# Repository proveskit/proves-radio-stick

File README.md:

# proves-radio-stick
New repo for working on a USB stick sized LoRa radio module. 

# Design Purpose
Being able to send and receive data using radios is one of the most fundemental functionalities of the satellite system. Right now, if we want to do anything with the radios we need to take a whole flight controller board out and get it setup to send and receive data. It would be nice to have an [RTL-SDR Style](https://www.rtl-sdr.com/buy-rtl-sdr-dvb-t-dongles/) USB dongle that can be used for testing and ground station purposes! 

# Design Requirements
- Employs an RP2040 Microcontroller (V0); RP2350 from V1 onward
- Onboard 3.3 V regulator for the microcontroller (LDO on V0, TPS62085 buck from V1); V2 radio runs from 5 V VBUS via ferrite
- Radio module: RFM9XW slot (V0), EByte E32-400M20S (V1), EByte E22-400M30S (V2)
- SMA Adaptor for the Antenna
- Is as comapct as possible 

# Versions
| Dir | MCU | Radio | Rail | Antenna | Notes |
|---|---|---|---|---|---|
| `provesradiostick_V0` | RP2040 | RFM9XW slot (SX127x) | 3V3 LDO | SMA | Original concept |
| `proves_radio_stick_V1` | RP2350 | EByte E32-400M20S (SX1278, 20 dBm) | 3V3 buck (TPS62085) | SMA | 4-layer 60 x 32.89 mm |
| `proves_radio_stick_V2` | RP2350 | EByte E22-400M30S (SX1268, 30 dBm) — same module as FC v5e | 3V3 buck + 5 V `RF_VCC` from VBUS via ferrite | SMA | 4-layer 80.5 x 32.89 mm; V1 stretched 20.5 mm to fit the 24 x 38.5 mm module |

## V2 radio pinout (RP2350 GPIO)
| E22 pin | Net | GPIO |
|---|---|---|
| NSS / SCK / MOSI / MISO | SPI1_CS0 / SPI1_SCK / SPI1_MOSI / SPI1_MISO | 9 / 10 / 11 / 8 |
| NRST | RF1_RST | 6 |
| BUSY | RF1_IO0 | 14 |
| DIO1 | RF1_IO1 | 15 |
| DIO2 | RF1_IO2 | 16 |
| RXEN / TXEN | RF1_RX_EN / RF1_TX_EN | 20 / 21 |
| VCC | RF_VCC (5 V, VBUS → FB1 → U19 TPS22918 load switch) | — |
| Radio power enable | RF_PWR_EN → U19 ON (10k pull-up to 3V3, default ON) | 18 |

V2 note: at 30 dBm the E22 draws ~650 mA peak on TX, above the 500 mA USB 2.0 default; use a USB 3 or high-current port for sustained TX. The 110 µF behind U19 soft-starts over ~3 ms (CT 1 nF, ~0.19 A inrush) so the host only sees ~11 µF at plug-in. Drive GPIO18 low then high to power-cycle the radio (hold NRST low and SPI lines low while off). V2 drops the 2.54 mm SWD pin header J1; use the JST-SH SWD connector J22. J3 screw terminal is sourced as Cixi Kefa KF128-2.54-10P (LCSC C474928), a 2.54 mm drop-in for the Phoenix MPT 0,5/10-2,54 footprint. J4 header and TP1–TP7 are not populated by JLC. Firmware differs from V1: SX1268 driver with BUSY handshake, not SX1278. Pin numbering differs from FC v5e (v5e uses SPI0 GPIO9-12, BUSY 13, DIO1 14, RXEN 22).

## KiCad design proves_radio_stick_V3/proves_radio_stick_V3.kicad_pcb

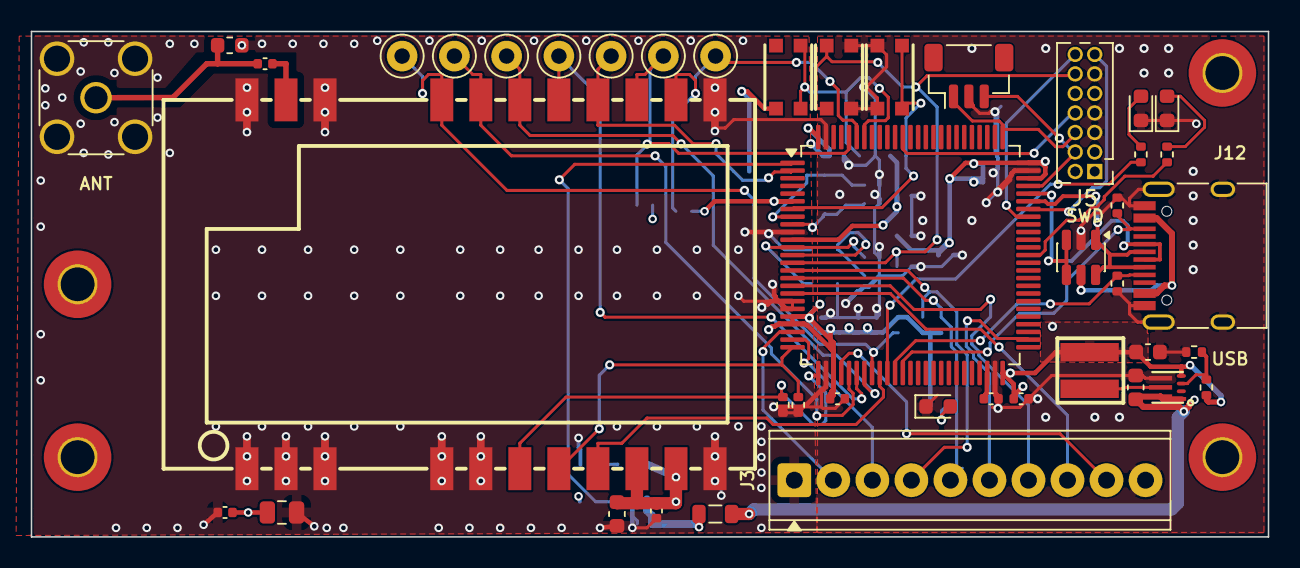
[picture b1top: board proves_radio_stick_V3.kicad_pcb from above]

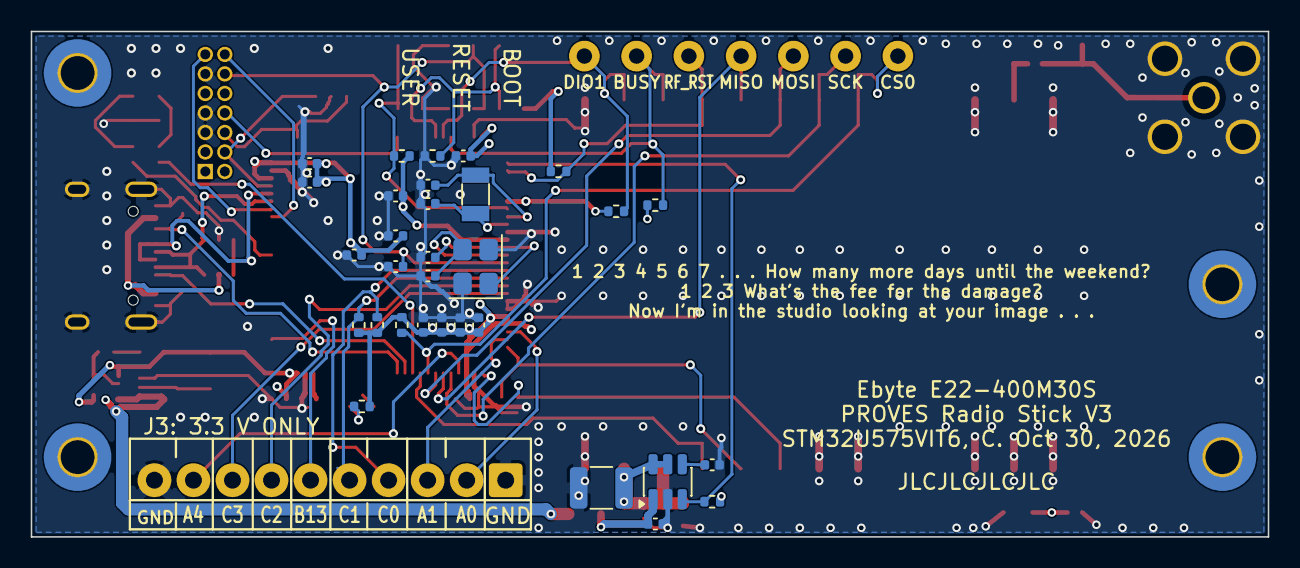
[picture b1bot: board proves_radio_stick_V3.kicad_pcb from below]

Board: 4 copper layers, 80.5 x 32.9 mm, 78 parts (31 on the bottom side), 51 nets.

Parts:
C1, C6, C101, C102, C103, C104, C105, C106, C108, C110, C112, C114: 100nF; C_0402_1005Metric
C3: 47uF; C_0805_2012Metric
C4: 100uF 10V; C_1210_3225Metric
C5, C15: 10uF; C_0603_1608Metric
C7: 100pF; C_0402_1005Metric
C14: 22uF; C_0603_1608Metric
C79: 1nF; C_0402_1005Metric
C80, C109, C111: 1uF; C_0402_1005Metric
C107, C113: 4.7uF; C_0402_1005Metric
C115, C116: 12pF; C_0402_1005Metric
C117, C118: 10pF; C_0402_1005Metric
D1, D2, D3: LED; LED_0603_1608Metric
FB1: BLM21PG600SN1D; L_0805_2012Metric
H1, H2, H3, H4: MountingHole; MountingHole_2.2mm_M2_Pad_TopBottom
J2: SMA antenna; SMA_Amphenol_132134_Vertical
J3: J3 breakout; TerminalBlock_Phoenix_MPT-0,5-10-2.54_1x10_P2.54mm_Horizont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
J5: STDC14; PinHeader_2x07_P1.27mm_Vertical
J12: USB-C (USB 2.0); USB_C_Receptacle_HRO_TYPE-C-31-M-12
J22: SWD (JST-SH); JST_SH_BM03B-SRSS-TB_1x03-1MP_P1.00mm_Vertical
L1: XFL4015-471MEC; IND-SMD_L4.0-W4.0_XFL4020-102MEB
L2: 120nH; L_0603_1608Metric
R3: 162k; R_0402_1005Metric
R4: 510k; R_0402_1005Metric
R5, R9, R11, R12, R95, R101, R102: 10k; R_0402_1005Metric
R13, R80, R103: 1k; R_0402_1005Metric
R14, R15, R104, R105: 4.7k; R_0402_1005Metric
R26, R27: 5.1k; R_0402_1005Metric
SW1, SW2, SW3: KMR2; BTN_KMR2_4.6X2.8
TP1, TP2, TP3, TP4, TP5, TP6, TP7: TestPoint; TestPoint_Keystone_5000-5004_Miniature
U1: STM32U575VIT6; LQFP-100_14x14mm_P0.5mm
U2: TPS62085RLTR; VSON-7_L2.0-W2.0-P0.5-TL
U3: E22-400M30S; WIRELM-SMD_E22-400M30S
U4: USBLC6-2SC6; SOT-23-6
U19: TPS22918DBVR; SOT-23-6
Y101: 16MHz; Crystal_SMD_3225-4Pin_3.2x2.5mm
Y102: 32.768kHz; Crystal_SMD_3215-2Pin_3.2x1.5mm

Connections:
+3V3: C1.1, C3.1, C14.1, C101.1, C102.1, C103.1, C104.1, C105.1, C106.1, C107.1, C108.1, C109.1, C110.1, C111.1, C112.1, J5.3, L1.2, R4.1, R5.2, R9.2, R14.1, R15.1, R80.1, R95.2, R102.1, R104.1, R105.1, SW1.A, SW1.A', U1.6, U1.11, U1.21, U1.22, U1.28, U1.50, U1.73, U1.75, U1.100, U2.4 (VOS)
/BOOT0: R101.1, SW1.B, SW1.B', U1.94
/LED2_A: D2.2, R103.2
/OSC32_IN: C117.1, U1.8, Y102.1
/OSC32_OUT: C118.1, U1.9, Y102.2
/OSC_IN: C115.1, U1.12, Y101.1
/OSC_OUT: C116.1, U1.13, Y101.3
/RF_ANT: C7.2, J2.1 (In), L2.1
/USER_BTN: R102.2, SW3.B, SW3.B', U1.7
/VCAP: C113.1, U1.48
Firmware_Active: R13.1, U1.35
GND: C1.2, C3.2, C4.2, C5.2, C6.2, C14.2, C15.2, C79.2, C80.2, C101.2, C102.2, C103.2, C104.2, C105.2, C106.2, C107.2, C108.2, C109.2, C110.2, C111.2, C112.2, C113.2, C114.2, C115.2, C116.2, C117.2, C118.2, D1.1 (K), D2.1, D3.1 (K), J2.2 (Ext), J3.1, J3.10, J5.5, J5.7, J5.11, J12.A1 (GND), J12.A12 (GND), J12.B1 (GND), J12.B12 (GND), J12.S1 (SHIELD), J22.2, L2.2, R3.2, R11.1, R12.1, R26.1, R27.1, R101.2, SW2.B, SW2.B', SW3.A, SW3.A', U1.10, U1.19, U1.20, U1.27, U1.49, U1.74, U1.99, U2.5 (GND), U3.1, U3.2, U3.3, U3.4, U3.5, U3.11, U3.12, U3.20, U3.22, U4.2, U19.2, Y101.2, Y101.4
J3_IO1: J3.2, U1.23
J3_IO2: J3.3, U1.24
J3_IO3: J3.4, R104.2, U1.15
J3_IO4: J3.5, R105.2, U1.16
J3_IO5: J3.6, U1.52
J3_IO6: J3.7, U1.17
J3_IO7: J3.8, U1.18
J3_IO8: J3.9, U1.29
unnamed: D1.2 (A), R13.2
unnamed: D3.2 (A), R80.2
unnamed: R3.1, R4.2, U2.3 (FB)
unnamed: L1.1, U2.6 (SW)
unnamed: C7.1, U3.21
unnamed: C79.1, U19.4
RF1_IO0: R14.2, TP5.1, U1.96, U3.14
RF1_IO1: R15.2, TP6.1, U1.95, U3.13
RF1_IO2: U1.34, U3.8
RF1_RST: R5.1, TP7.1, U1.2, U3.15
RF1_RX_EN: R11.2, U1.26, U3.6
RF1_TX_EN: R12.2, U1.25, U3.7
RF_5V_IN: C80.1, FB1.2, U19.1
RF_PWR_EN: R95.1, U1.1, U19.3
RF_VCC: C4.1, C5.1, C6.1, U3.9, U3.10, U19.5, U19.6
RX: J5.13, U1.69
SPI1_CS0: R9.1, TP2.1, U1.33, U3.19
SPI1_MISO: TP1.1, U1.31, U3.16
SPI1_MOSI: TP4.1, U1.32, U3.17
SPI1_SCK: TP3.1, U1.30, U3.18
SWCLK: J5.6, J22.1, U1.76
SWDIO: J5.4, J22.3, U1.72
SWO: J5.8, U1.89
TX: J5.14, U1.68
USB_CC1_SENSE: J12.A5 (CC1), R26.2, U1.36
USB_CC2_SENSE: J12.B5 (CC2), R27.2, U1.37
USB_D+: J12.A6 (D+), J12.B6 (D+), U1.71, U4.3, U4.4
USB_D-: J12.A7 (D-), J12.B7 (D-), U1.70, U4.1, U4.6
USER_LED: R103.1, U1.63
VBUS: C15.1, FB1.1, J12.A4 (VBUS), J12.A9 (VBUS), J12.B4 (VBUS), J12.B9 (VBUS), U2.1 (EN), U2.7 (VIN), U4.5
~RESET: C114.1, J5.12, SW2.A, SW2.A', U1.14

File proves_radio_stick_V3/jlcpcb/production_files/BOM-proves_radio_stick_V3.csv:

Comment,Designator,Footprint,LCSC,Quantity
100n,"C1,C101,C102,C103,C104,C105,C106,C108,C110,C112,C114",C_0402_1005Metric,C1525,11
47uF,C3,C_0805_2012Metric,C16780,1
100uF 10V,C4,C_1210_3225Metric,C84455,1
10uF,"C5,C15",C_0603_1608Metric,C19702,2
100nF,C6,C_0402_1005Metric,C1525,1
100pF,C7,C_0402_1005Metric,C1546,1
22uF,C14,C_0603_1608Metric,C59461,1
1nF,C79,C_0402_1005Metric,C1523,1
1uF,C80,C_0402_1005Metric,C52923,1
4.7u,"C107,C113",C_0402_1005Metric,C23733,2
1u,"C109,C111",C_0402_1005Metric,C52923,2
12p,"C115,C116",C_0402_1005Metric,C1547,2
10p,"C117,C118",C_0402_1005Metric,C32949,2
LED,"D1,D2,D3",LED_0603_1608Metric,C2290,3
BLM21PG600SN1D,FB1,L_0805_2012Metric,C18305,1
Conn_Coaxial,J2,SMA_Amphenol_132134_Vertical,C3174425,1
Screw_Terminal_01x10,J3,"TerminalBlock_Phoenix_MPT-0,5-10-2.54_1x10_P2.54mm_Horizontal",C474928,1
STDC14,J5,PinHeader_2x07_P1.27mm_Vertical,C22438122,1
USB_C_Receptacle_USB2.0_16P,J12,USB_C_Receptacle_HRO_TYPE-C-31-M-12,C165948,1
SWD Port,J22,JST_SH_BM03B-SRSS-TB_1x03-1MP_P1.00mm_Vertical,C160389,1
XFL4015-471MEC,L1,IND-SMD_L4.0-W4.0_XFL4020-102MEB,C18221164,1
120nH,L2,L_0603_1608Metric,C86138,1
162k,R3,R_0402_1005Metric,C54068,1
510k,R4,R_0402_1005Metric,C11616,1
10k,"R5,R9,R11,R12,R95,R101,R102",R_0402_1005Metric,C25744,7
1k,"R13,R80,R103",R_0402_1005Metric,C11702,3
5.1k,"R26,R27",R_0402_1005Metric,C25905,2
4.7k,"R104,R105",R_0402_1005Metric,C25900,2
KMR2,"SW1,SW2,SW3",BTN_KMR2_4.6X2.8,C72443,3
STM32U575VIT6,U1,LQFP-100_14x14mm_P0.5mm,C5270999,1
TPS62085RLTR,U2,VSON-7_L2.0-W2.0-P0.5-TL,C130072,1
E22-400M30S,U3,WIRELM-SMD_E22-400M30S,C411292,1
USBLC6-2SC6,U4,SOT-23-6,C7519,1
TPS22918DBVR,U19,SOT-23-6,C131941,1
16MHz,Y101,Crystal_SMD_3225-4Pin_3.2x2.5mm,C13738,1
32.768kHz,Y102,Crystal_SMD_3215-2Pin_3.2x1.5mm,C97604,1

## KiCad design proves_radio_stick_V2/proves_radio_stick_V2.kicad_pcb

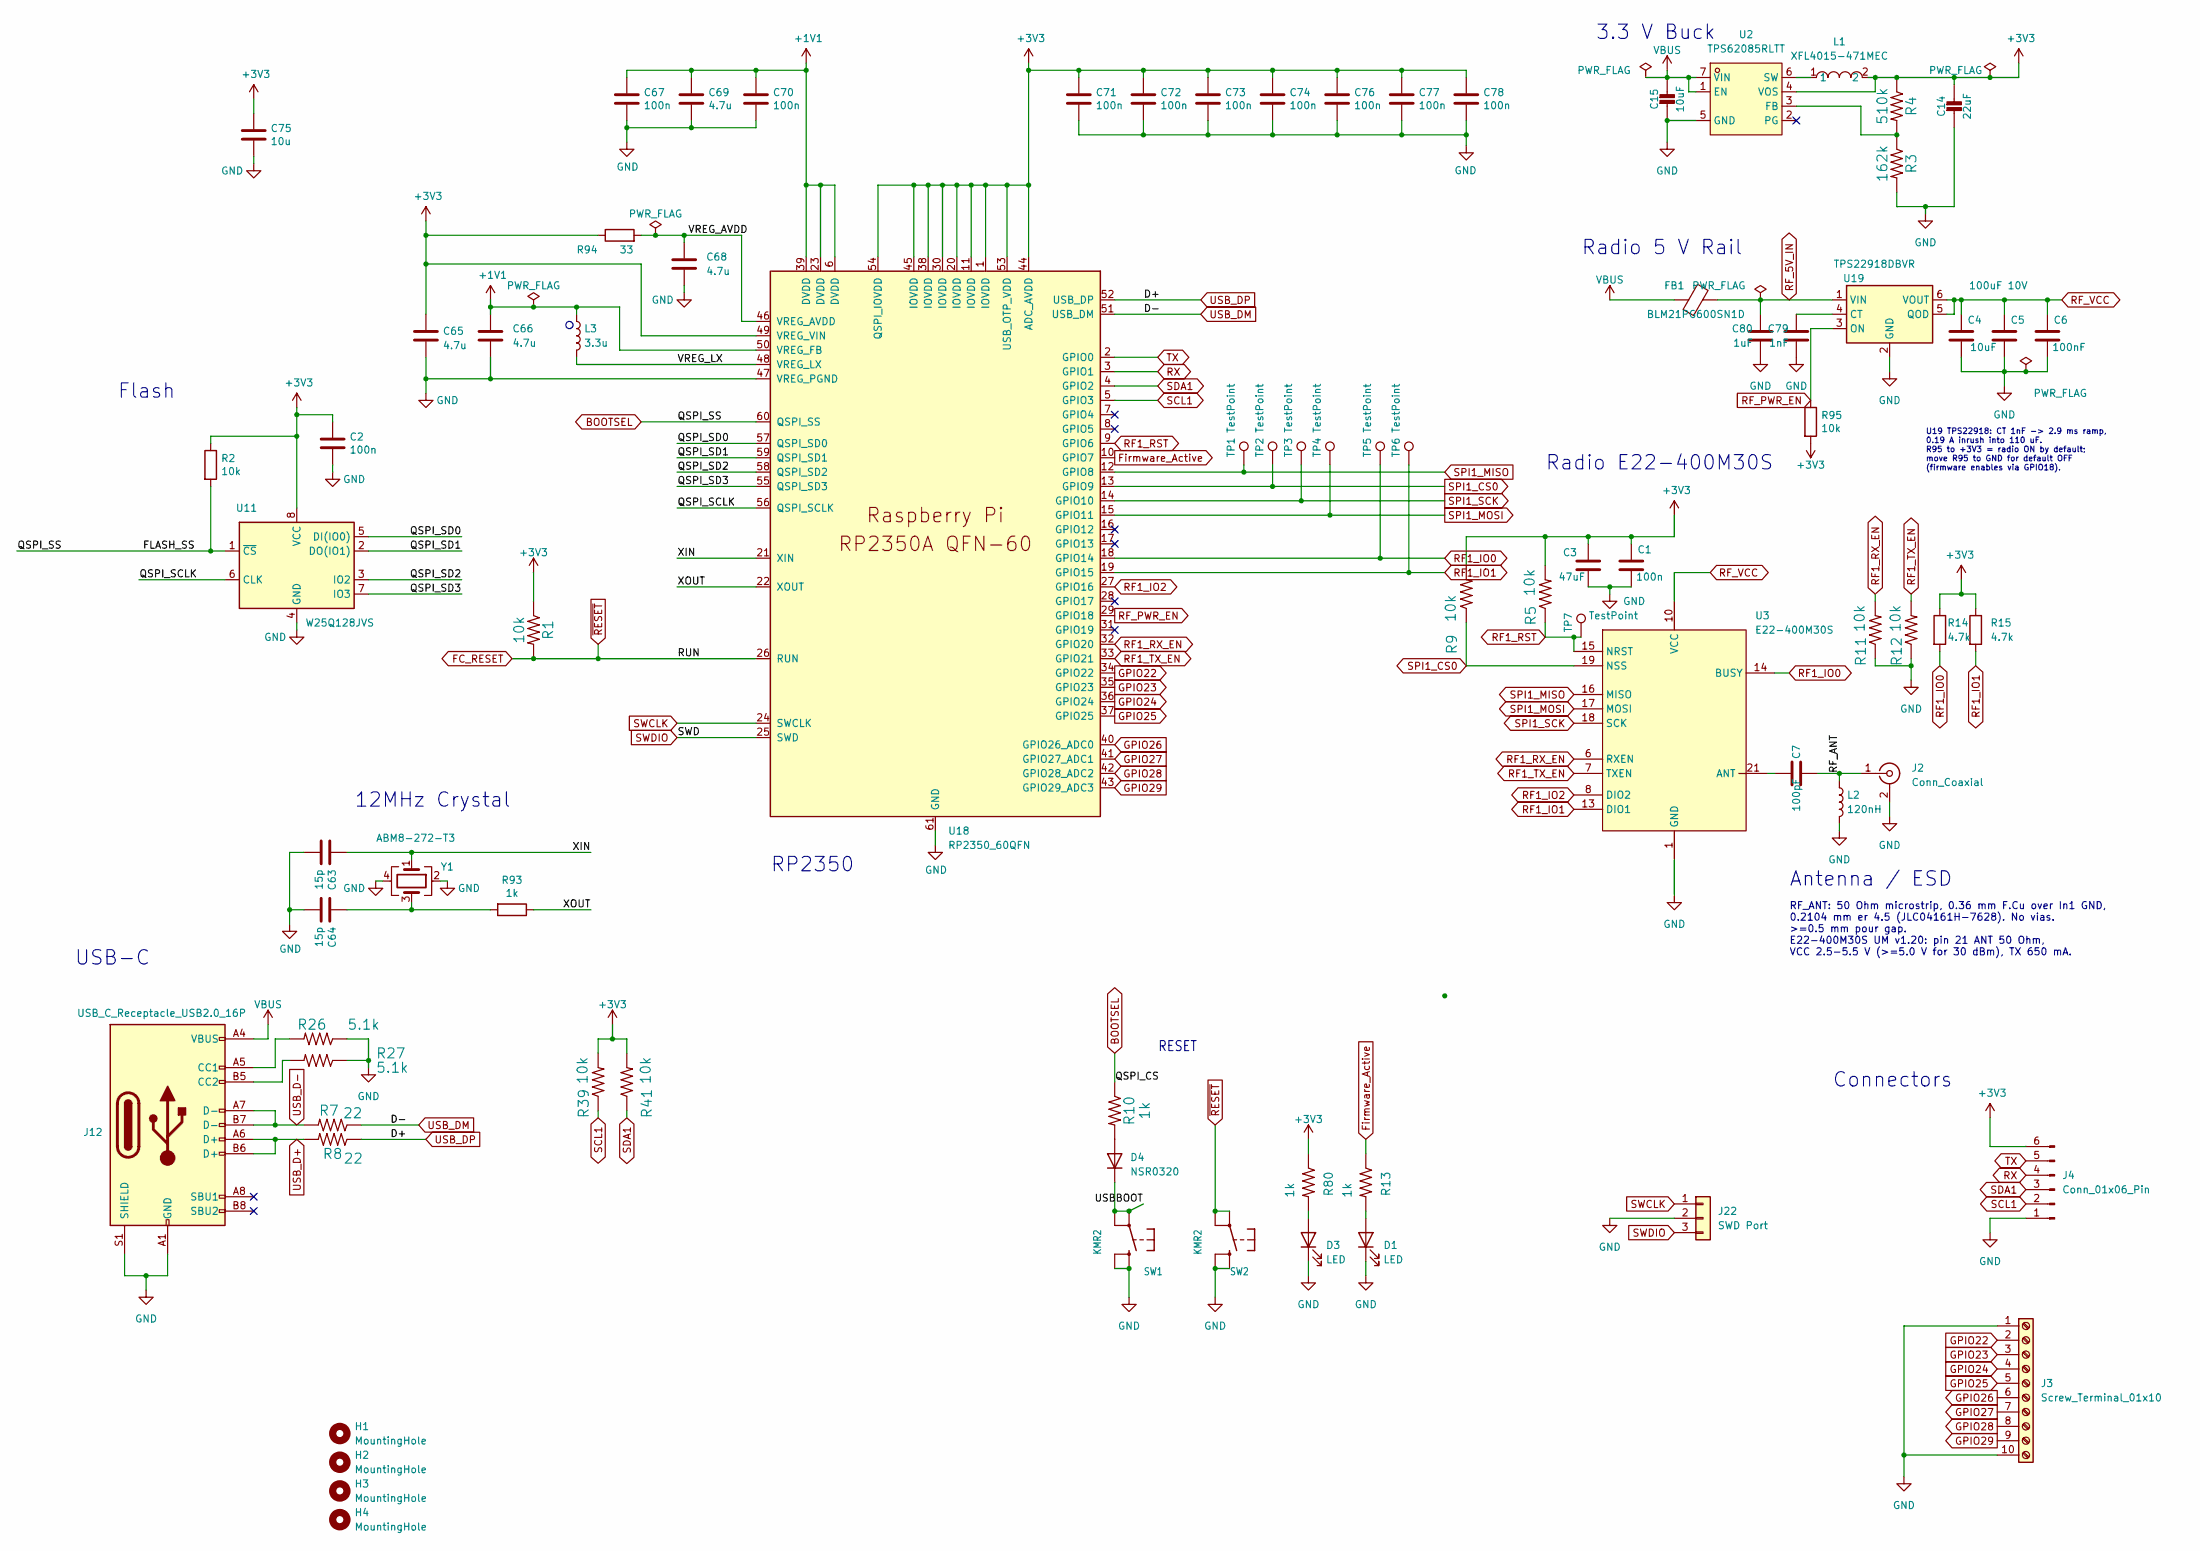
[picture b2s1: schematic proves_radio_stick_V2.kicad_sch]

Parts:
C1, C2, C67, C70, C71, C72, C73, C74, C76, C77, C78: 100n; C_0402_1005Metric; LCSC Part C1525
C3: 47uF; C_0805_2012Metric; LCSC Part C16780
C4: 100uF 10V; C_1210_3225Metric; LCSC Part C84455
C5, C15: 10uF; C_0603_1608Metric; LCSC Part C19702
C6: 100nF; C_0402_1005Metric; LCSC Part C1525
C7: 100pF; C_0402_1005Metric; LCSC Part C1546
C14: 22uF; C_0603_1608Metric; LCSC Part C59461
C63, C64: 15p; C_0402_1005Metric; LCSC Part C1548
C65, C66: 4.7u; C_0402_1005Metric_small_pads; LCSC Part C23733
C68, C69: 4.7u; C_0402_1005Metric; LCSC Part C23733
C75: 10u; C_0603_1608Metric; LCSC Part C19702
C79: 1nF; C_0402_1005Metric; LCSC Part C1523
C80: 1uF; C_0402_1005Metric; LCSC Part C52923
D1, D3: LED; LED_0603_1608Metric; LCSC Part C2290
D4: NSR0320; D_SOD-323F; LCSC Part C48192
FB1: BLM21PG600SN1D; L_0805_2012Metric; LCSC Part C18305
H1, H2, H3, H4: MountingHole; MountingHole_2.2mm_M2_Pad_TopBottom
J2: Conn_Coaxial; SMA_Amphenol_132134_Vertical; LCSC Part C3174425
J3: Screw_Terminal_01x10; TerminalBlock_Phoenix_MPT-0,5-10-2.54_1x10_P2.54mm_Horizont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; MPN KF128-2.54-10P; LCSC Part C474928
J4: Conn_01x06_Pin; PinHeader_1x06_P2.54mm_Vertical
J12: USB_C_Receptacle_USB2.0_16P; USB_C_Receptacle_HRO_TYPE-C-31-M-12; LCSC Part C165948
J22: SWD Port; JST_SH_BM03B-SRSS-TB_1x03-1MP_P1.00mm_Vertical; LCSC Part C160389
L1: XFL4015-471MEC; IND-SMD_L4.0-W4.0_XFL4020-102MEB; LCSC Part C18221164
L2: 120nH; L_0603_1608Metric; MPN LQW18ANR12G00D; LCSC Part C86138
L3: 3.3u; L_pol_2016; LCSC Part C42411119
R1, R2, R5, R9, R11, R12, R39, R41, R95: 10k; R_0402_1005Metric; LCSC Part C25744
R3: 162k; R_0402_1005Metric; LCSC Part C54068
R4: 510k; R_0402_1005Metric; LCSC Part C11616
R7, R8: 22; R_0402_1005Metric; LCSC Part C25092
R10, R13, R80, R93: 1k; R_0402_1005Metric; LCSC Part C11702
R14, R15: 4.7k; R_0402_1005Metric; LCSC Part C25900
R26, R27: 5.1k; R_0402_1005Metric; LCSC Part C25905
R94: 33; R_0402_1005Metric; LCSC Part C25105
SW1, SW2: KMR2; BTN_KMR2_4.6X2.8; LCSC Part C72443
TP1, TP2, TP3, TP4, TP5, TP6, TP7: TestPoint; TestPoint_Keystone_5000-5004_Miniature
U2: TPS62085RLTT; VSON-7_L2.0-W2.0-P0.5-TL; LCSC Part C2070694
U3: E22-400M30S; WIRELM-SMD_E22-400M30S; MPN E22-400M30S; LCSC Part C411292
U11: W25Q128JVS; SOIC-8_5.3x5.3mm_P1.27mm; LCSC Part C97521
U18: RP2350_60QFN; RP2350-QFN-60-1EP_7x7_P0.4mm_EP3.4x3.4mm_ThermalVias; LCSC Part C42411118
U19: TPS22918DBVR; SOT-23-6; LCSC Part C131941
Y1: ABM8-272-T3; Crystal_SMD_3225-4Pin_3.2x2.5mm; LCSC Part C20625731

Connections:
+1V1: C66.1, C67.1, C69.1, C70.1, L3.1, U18.6 (DVDD), U18.23 (DVDD), U18.39 (DVDD), U18.50 (VREG_FB)
+3V3: C1.1, C2.1, C3.1, C14.1, C65.1, C71.1, C72.1, C73.1, C74.1, C75.1, C76.1, C77.1, C78.1, J4.6, L1.2, R1.1, R2.1, R4.1, R5.2, R9.2, R14.1, R15.1, R39.2, R41.2, R80.1, R94.1, R95.2, U2.4 (VOS), U11.8 (VCC), U18.1 (IOVDD), U18.11 (IOVDD), U18.20 (IOVDD), U18.30 (IOVDD), U18.38 (IOVDD), U18.44 (ADC_AVDD), U18.45 (IOVDD), U18.49 (VREG_VIN), U18.53 (USB_OTP_VDD), U18.54 (QSPI_IOVDD)
/QSPI_SCLK: U11.6 (CLK), U18.56 (QSPI_SCLK)
/QSPI_SD0: U11.5 (DI(IO0)), U18.57 (QSPI_SD0)
/QSPI_SD1: U11.2 (DO(IO1)), U18.59 (QSPI_SD1)
/QSPI_SD2: U11.3 (IO2), U18.58 (QSPI_SD2)
/QSPI_SD3: U11.7 (IO3), U18.55 (QSPI_SD3)
/RF_ANT: C7.2, J2.1 (In), L2.1
/USBBOOT: D4.1 (K), SW1.A, SW1.A' (P1)
/VREG_AVDD: C68.1, R94.2, U18.46 (VREG_AVDD)
/VREG_LX: L3.2, U18.48 (VREG_LX)
/XIN: C63.1, U18.21 (XIN), Y1.1
/XOUT: R93.1, U18.22 (XOUT)
BOOTSEL: R2.2, R10.1, U11.1 (~CS), U18.60 (QSPI_SS)
FC_RESET: R1.2, SW2.A, SW2.A' (P1), U18.26 (RUN)
Firmware_Active: R13.1, U18.10 (GPIO7)
GND: C1.2, C2.2, C3.2, C4.2, C5.2, C6.2, C14.2, C15.2, C63.2, C64.2, C65.2, C66.2, C67.2, C68.2, C69.2, C70.2, C71.2, C72.2, C73.2, C74.2, C75.2, C76.2, C77.2, C78.2, C79.2, C80.2, D1.1 (K), D3.1 (K), J2.2 (Ext), J3.1, J3.10, J4.1, J12.A1 (GND), J12.A12 (GND), J12.B1 (GND), J12.B12 (GND), J12.S1 (SHIELD), J22.2, L2.2, R3.2, R11.1, R12.1, R26.1, R27.1, SW1.B (S), SW1.B' (S1), SW2.B (S), SW2.B' (S1), U2.5 (GND), U3.1 (GND), U3.2 (GND), U3.3 (GND), U3.4 (GND), U3.5 (GND), U3.11 (GND), U3.12 (GND), U3.20 (GND), U3.22 (GND), U11.4 (GND), U18.47 (VREG_PGND), U18.61 (GND), U19.2 (GND), Y1.2, Y1.4
GPIO22: J3.2, U18.34 (GPIO22)
GPIO23: J3.3, U18.35 (GPIO23)
GPIO24: J3.4, U18.36 (GPIO24)
GPIO25: J3.5, U18.37 (GPIO25)
GPIO26: J3.6, U18.40 (GPIO26_ADC0)
GPIO27: J3.7, U18.41 (GPIO27_ADC1)
GPIO28: J3.8, U18.42 (GPIO28_ADC2)
GPIO29: J3.9, U18.43 (GPIO29_ADC3)
unnamed: C64.1, R93.2, Y1.3
unnamed: D1.2 (A), R13.2
unnamed: D3.2 (A), R80.2
unnamed: D4.2 (A), R10.2
unnamed: J12.A5 (CC1), R26.2
unnamed: J12.B5 (CC2), R27.2
unnamed: R3.1, R4.2, U2.3 (FB)
unnamed: L1.1, U2.6 (SW)
unnamed: C7.1, U3.21 (ANT)
unnamed: C79.1, U19.4 (CT)
RF1_IO0: R14.2, TP5.1, U3.14 (BUSY), U18.18 (GPIO14)
RF1_IO1: R15.2, TP6.1, U3.13 (DIO1), U18.19 (GPIO15)
RF1_IO2: U3.8 (DIO2), U18.27 (GPIO16)
RF1_RST: R5.1, TP7.1, U3.15 (NRST), U18.9 (GPIO6)
RF1_RX_EN: R11.2, U3.6 (RXEN), U18.32 (GPIO20)
RF1_TX_EN: R12.2, U3.7 (TXEN), U18.33 (GPIO21)
RF_5V_IN: C80.1, FB1.2, U19.1 (VIN)
RF_PWR_EN: R95.1, U18.29 (GPIO18), U19.3 (ON)
RF_VCC: C4.1, C5.1, C6.1, U3.9 (VCC), U3.10 (VCC), U19.5 (QOD), U19.6 (VOUT)
RX: J4.4, U18.3 (GPIO1)
SCL1: J4.2, R39.1, U18.5 (GPIO3)
SDA1: J4.3, R41.1, U18.4 (GPIO2)
SPI1_CS0: R9.1, TP2.1, U3.19 (NSS), U18.13 (GPIO9)
SPI1_MISO: TP1.1, U3.16 (MISO), U18.12 (GPIO8)
SPI1_MOSI: TP4.1, U3.17 (MOSI), U18.15 (GPIO11)
SPI1_SCK: TP3.1, U3.18 (SCK), U18.14 (GPIO10)
SWCLK: J22.1, U18.24 (SWCLK)
SWDIO: J22.3, U18.25 (SWD)
TX: J4.5, U18.2 (GPIO0)
USB_D+: J12.A6 (D+), J12.B6 (D+), R8.2
USB_D-: J12.A7 (D-), J12.B7 (D-), R7.2
USB_DM: R7.1, U18.51 (USB_DM)
USB_DP: R8.1, U18.52 (USB_DP)
VBUS: C15.1, FB1.1, J12.A4 (VBUS), J12.A9 (VBUS), J12.B4 (VBUS), J12.B9 (VBUS), U2.1 (EN), U2.7 (VIN)

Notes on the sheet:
RESET
Flash
12MHz Crystal
RF_ANT: 50 Ohm microstrip, 0.36 mm F.Cu over In1 GND, 0.2104 mm er 4.5 (JLC04161H-7628). No vias. >=0.5 mm pour gap. E22-400M30S UM v1.20: pin 21 ANT 50 Ohm, VCC 2.5-5.5 V (>=5.0 V for 30 dBm), TX 650 mA.
U19 TPS22918: CT 1nF -> 2.9 ms ramp, 0.19 A inrush into 110 uF. R95 to +3V3 = radio ON by default; move R95 to GND for default OFF (firmware enables via GPIO18).
3.3 V Buck
Radio 5 V Rail
Radio E22-400M30S
Antenna / ESD
Connectors
USB-C
RP2350

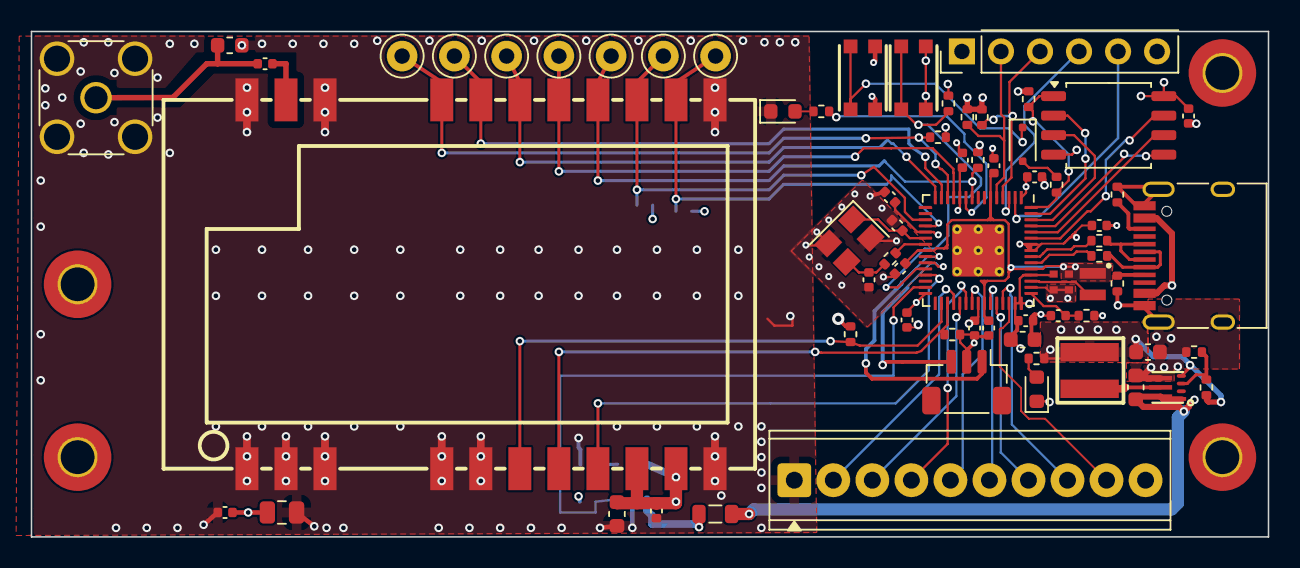
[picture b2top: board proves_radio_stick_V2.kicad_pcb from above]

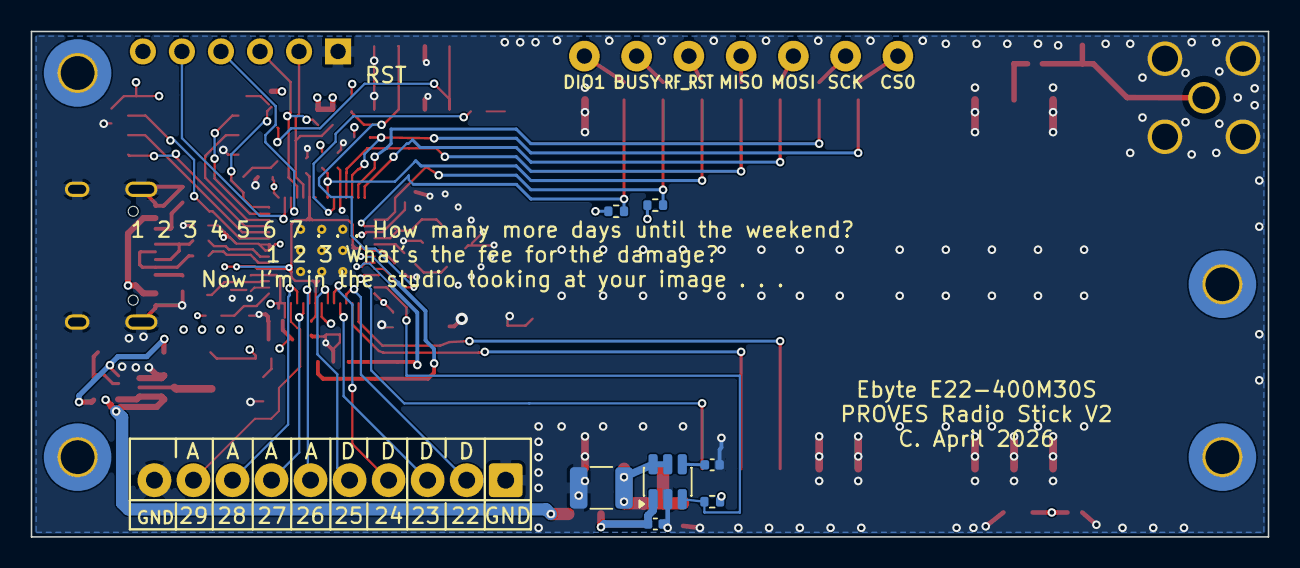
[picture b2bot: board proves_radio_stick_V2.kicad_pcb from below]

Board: 4 copper layers, 80.5 x 32.9 mm, 80 parts (7 on the bottom side), 59 nets.

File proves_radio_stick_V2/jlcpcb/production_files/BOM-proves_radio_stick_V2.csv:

Comment,Designator,Footprint,LCSC,Quantity
100uF 10V,C4,C_1210_3225Metric,C84455,1
1nF,C79,C_0402_1005Metric,C1523,1
1uF,C80,C_0402_1005Metric,C52923,1
4.7k,"R14,R15",R_0402_1005Metric,C25900,2
10k,"R95,R1,R2,R5,R9,R11,R12,R39,R41",R_0402_1005Metric,C25744,9
TPS22918DBVR,U19,SOT-23-6,C131941,1
100n,"C1,C2,C67,C70,C71,C72,C73,C74,C76,C77,C78",C_0402_1005Metric,C1525,11
47uF,C3,C_0805_2012Metric,C16780,1
10uF,"C5,C15",C_0603_1608Metric,C19702,2
100nF,C6,C_0402_1005Metric,C1525,1
100pF,C7,C_0402_1005Metric,C1546,1
22uF,C14,C_0603_1608Metric,C59461,1
15p,"C63,C64",C_0402_1005Metric,C1548,2
4.7u,"C65,C66",C_0402_1005Metric_small_pads,C23733,2
4.7u,"C68,C69",C_0402_1005Metric,C23733,2
10u,C75,C_0603_1608Metric,C19702,1
LED,"D1,D3",LED_0603_1608Metric,C2290,2
NSR0320,D4,D_SOD-323F,C48192,1
BLM21PG600SN1D,FB1,L_0805_2012Metric,C18305,1
Conn_Coaxial,J2,SMA_Amphenol_132134_Vertical,C3174425,1
Screw_Terminal_01x10,J3,"TerminalBlock_Phoenix_MPT-0,5-10-2.54_1x10_P2.54mm_Horizontal",C474928,1
USB_C_Receptacle_USB2.0_16P,J12,USB_C_Receptacle_HRO_TYPE-C-31-M-12,C165948,1
SWD Port,J22,JST_SH_BM03B-SRSS-TB_1x03-1MP_P1.00mm_Vertical,C160389,1
XFL4015-471MEC,L1,IND-SMD_L4.0-W4.0_XFL4020-102MEB,C18221164,1
120nH,L2,L_0603_1608Metric,C86138,1
3.3u,L3,L_pol_2016,C42411119,1
162k,R3,R_0402_1005Metric,C54068,1
510k,R4,R_0402_1005Metric,C11616,1
22,"R7,R8",R_0402_1005Metric,C25092,2
1k,"R10,R13,R80,R93",R_0402_1005Metric,C11702,4
5.1k,"R26,R27",R_0402_1005Metric,C25905,2
33,R94,R_0402_1005Metric,C25105,1
KMR2,"SW1,SW2",BTN_KMR2_4.6X2.8,C72443,2
TPS62085RLTT,U2,VSON-7_L2.0-W2.0-P0.5-TL,C2070694,1
E22-400M30S,U3,WIRELM-SMD_E22-400M30S,C411292,1
W25Q128JVS,U11,SOIC-8_5.3x5.3mm_P1.27mm,C97521,1
RP2350_60QFN,U18,RP2350-QFN-60-1EP_7x7_P0.4mm_EP3.4x3.4mm_ThermalVias,C42411118,1
ABM8-272-T3,Y1,Crystal_SMD_3225-4Pin_3.2x2.5mm,C20625731,1

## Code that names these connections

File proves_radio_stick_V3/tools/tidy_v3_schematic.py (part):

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    ('3  RADIO 5 V SWITCH (U19)', [('rail', 237, 22)], [
        ('RF_VCC = VBUS via FB1 and load switch U19 (>= 5 V for 30 dBm).\n'
         'CT 1 nF -> 2.9 ms ramp, 0.19 A inrush into 110 uF.\n'
         'ON = RF_PWR_EN (PE2). R95 to +3V3 = radio ON by default;\n'
         'move R95 to GND for default OFF.', 'rail^', 0, 3.81, 1.27)]),
    ('4  MCU SUPPORT', [('decoup', 17, 112), ('hse', 17, 168), ('lse', 53, 168),
                        ('boot0', 17, 214), ('button', 53, 214)], [
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         '(>= 5.0 V for 30 dBm), TX 650 mA.', 'tps', 58, -2.54, 1.27)]),
    ('7  DEBUG (J5, J22)', [('stdc14', 346, 22), ('swd', 346, 52)], [
        ('J5 STDC14 fits STLINK-V3MINIE.\nPins 13/14 = T_VCP_RX/T_VCP_TX:\n'
         'USART1 PA9 TX / PA10 RX.\nJ22 JST-SH: SWD only (no SWO).', 'swd^', 0, 3.81, 1.27)]),
    ('8  J3 BREAKOUT (screw terminal)', [('j3', 320, 112), ('i2c', 375, 112)], [
        ('I2C3 pull-ups', 'i2c', 0, -3.81, H),
        ('3.3 V logic only: J3_IO1-8 go straight to MCU pins\n'
         '(no buffer or protection). IO3/IO4 = I2C3 SCL/SDA,\n'
         'IO5-IO8 = SPI2. Full map: pinmap/README.md.', 'j3^', 0, 3.81, 1.27)]),
    ('9  RESET AND LEDS', [('reset', 320, 178), ('leds', 340, 178), ('uled', 370, 178)], [
        ('SW2 pulls ~{RESET} (NRST) low. D3 = +3V3 power,\nD1 = Firmware_Active (PB0), D2 = USER_LED (PC6).',
         'leds^', -20, 3.81, 1.27)]),
    ('10  MOUNTING', [('holes', 198, 243)], []),
]
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
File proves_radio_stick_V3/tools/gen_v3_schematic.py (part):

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SUPPLY = [n for n, v in PIN_NAME.items() if v in ('VDD', 'VDDA', 'VDDUSB', 'VBAT')]
GROUND = [n for n, v in PIN_NAME.items() if v in ('VSS', 'VSSA')]
mcu_nets[PIN_NUM['NRST']] = 'G:~{RESET}'
mcu_nets[PIN_NUM['VCAP']] = 'L:VCAP'
mcu_nets[PIN_NUM['VREF+']] = 'P:+3V3'
mcu_nets[PIN_NUM['VREF-']] = 'P:GND'
for n in PIN_NAME:  # every I/O the pin map leaves free gets a no-connect flag
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assert (64.77, 194.31) in v2_ends and (63.5, 201.93) in v2_ends, 'V2 CC routing moved'
wire(64.77, 194.31, 64.77, 189.23)
junction(64.77, 194.31)
label('USB_CC1_SENSE', 64.77, 189.23, (0, -1), True)
# Move R26/R27's GND symbol right so the CC2 label clears it.
for sym in find(t, 'symbol'):
    if ref_of(sym) == '#PWR090':
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wire(78.74, 198.12, 92.71, 198.12)
wire(63.5, 201.93, 68.58, 201.93)
junction(63.5, 201.93)
label('USB_CC2_SENSE', 68.58, 201.93, (1, 0), True)

# ---------------------------------------------------------------- finish

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t[si:si] = new

# V2 notes that name RP2350 pins.
out = dump(t).replace('(firmware enables via GPIO18)', '(firmware enables via PE2)')
open(OUT, 'w').write(out + '\n')
print('removed:', ' '.join(sorted(r for r in removed if not r.startswith('#'))))
print('added %d items -> %s' % (len(new), OUT))
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
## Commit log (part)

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2025-03-18 Created V0a Project
2025-05-09 Removed Unused Files
2025-05-10 Created Radio Stick V1 Project
2025-06-15 Removed V0a Project
2025-10-04 Added E22-400M
2025-10-05 Initial TPS62 Layout
2025-10-05 Removed 3v3 Linear Regulator
2026-04-17 RP2350 and Support Circuits Layout
2026-04-17 Added E32 Footprint
2026-04-17 Initial Layout Complete
2026-04-17 Initial Production Files
2026-04-17 Updated DRC
2026-04-17 Removed Lock Files
2026-04-21 Updated with Screw Terminals and Vias
2026-04-21 Updated Prod Files
